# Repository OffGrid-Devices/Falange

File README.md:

# OffGrid-Devices Falange
Arduino-based delay weirdo

[BOM](https://docs.google.com/spreadsheets/d/1_OFgzQ-Cf3UgnrHv29c7YLzdb8jIv9dC1f2YYJAlo-E/edit?usp=sharing)

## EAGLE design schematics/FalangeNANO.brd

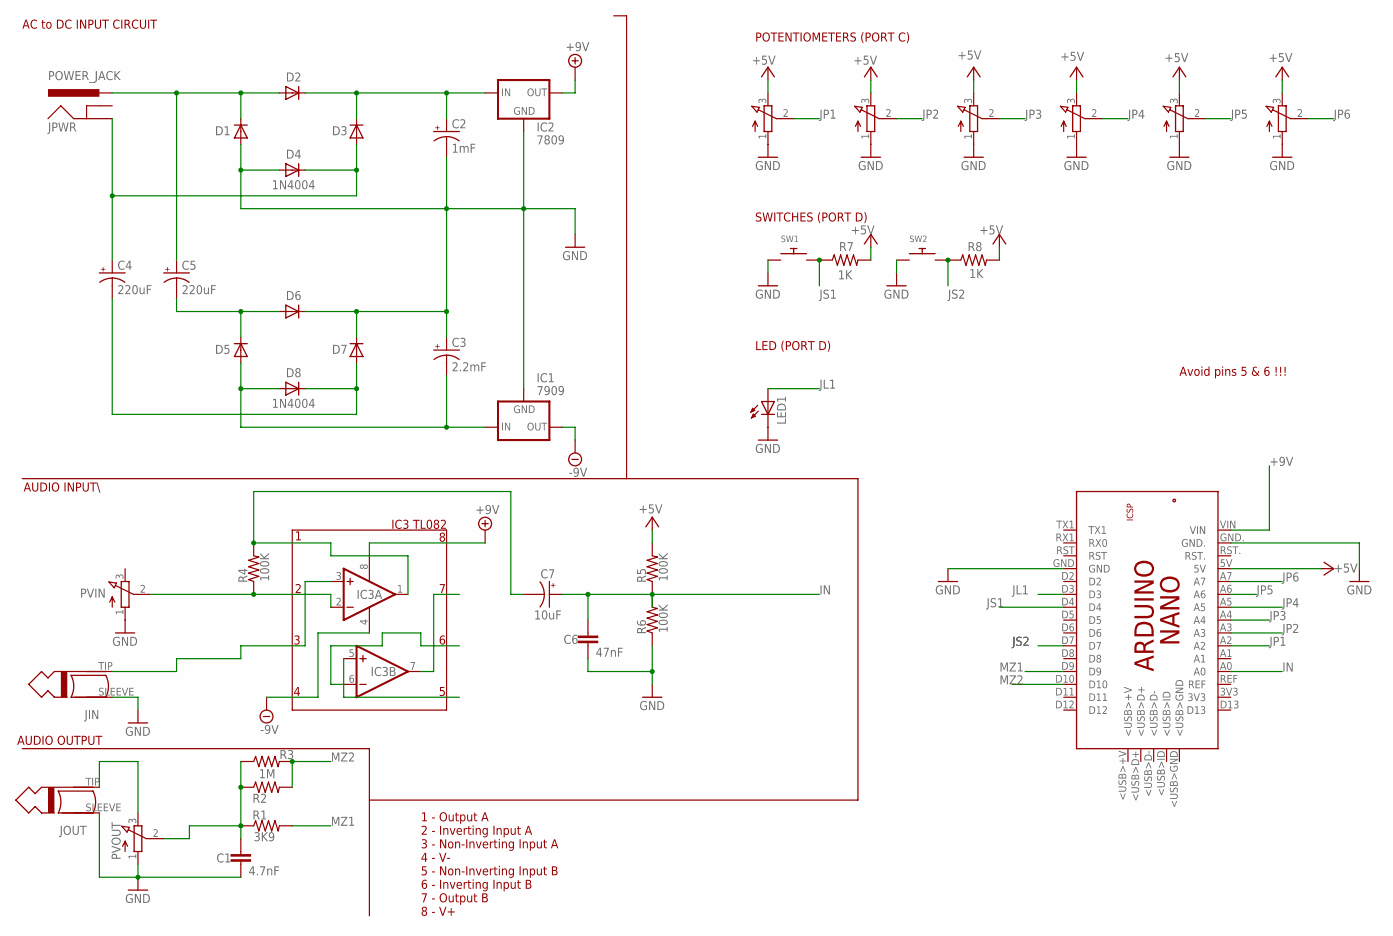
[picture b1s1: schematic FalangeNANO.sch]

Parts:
C1: 4.7nF; C050-025X075
C2: 1mF; E30-16
C3: 2.2mF; E35-16
C4, C5: 220uF; E5-10,5
C6: 47nF; C050-025X075
C7: 10uF; E2,5-6
D1, D2, D3, D4, D5, D6, D7, D8: 1N4004; DO41-10
IC1: 7909; 79XXL
IC2: 7809; 78XXL
IC3: TL082P; DIL08
JIN: MONO_PLUG; TWO_PADS
JOUT: MONO_PLUG; TWO_PADS
JPWR: POWER_JACK; POWER_JACK_PTH
LED1: LED3MM
P1, P2, P3, P4, P5, P6: 3RP/1610N
PCB1: ARDUINO_NANO
PVIN: 3RP/1610N
PVOUT: 3RP/1610N
R1: 3K9; AXIAL-0.3
R2, R3: 1M; AXIAL-0.3
R4, R5, R6: 100K; AXIAL-0.3
R7, R8: 1K; AXIAL-0.3
SW1, SW2: SWITCH_PUSHBUTTONEVQ-PE; TACT_PANA-EVQ

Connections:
+5V: P1.3 (E), P2.3 (E), P3.3 (E), P4.3 (E), P5.3 (E), P6.3 (E), PCB1.5V, R5.P$2 (2), R7.P$2 (2), R8.P$2 (2)
+9V: IC2.OUT, IC3.8 (V+), PCB1.VIN
-9V: IC1.OUT, IC3.4 (V-)
GND: C1.2, C2.-, C3.+, C6.2, D1.A, D4.A, D6.C, D7.C, IC1.GND, IC2.GND, JIN.SLEEVE, JOUT.SLEEVE, LED1.K (C), P1.1 (A), P2.1 (A), P3.1 (A), P4.1 (A), P5.1 (A), P6.1 (A), PCB1.GND, PCB1.GND., PVIN.1 (A), PVOUT.1 (A), R6.P$1 (1), SW1.P$1, SW2.P$1
IN: C6.1, C7.+, PCB1.A0, R5.P$1 (1), R6.P$2 (2)
JL1: LED1.A, PCB1.D3
JP1: P1.2 (S), PCB1.A2
JP2: P2.2 (S), PCB1.A3
JP3: P3.2 (S), PCB1.A4
JP4: P4.2 (S), PCB1.A5
JP5: P5.2 (S), PCB1.A6
JP6: P6.2 (S), PCB1.A7
JP8-2: C1.1, PVOUT.2 (S), R1.P$1 (1), R2.P$1 (1), R3.P$1 (1)
JP8-3: JOUT.TIP, PVOUT.3 (E)
JS1: PCB1.D4, R7.P$1 (1), SW1.P$2
JS2: PCB1.D7, R8.P$1 (1), SW2.P$2
MZ1: PCB1.D9, R1.P$2 (2)
MZ2: PCB1.D10, R2.P$2 (2), R3.P$2 (2)
unnamed: C5.-, D5.C, D6.A
unnamed: C4.-, D7.A, D8.C
unnamed: C2.+, D2.C, D3.C, IC2.IN
unnamed: C3.-, D5.A, D8.A, IC1.IN
unnamed: C7.-, IC3.1 (OUT), R4.P$2 (2)
unnamed: IC3.2 (-IN), PVIN.2 (S), R4.P$1 (1)
unnamed: IC3.3 (+IN), JIN.TIP
PWRSLV: C4.+, D3.A, D4.C, JPWR.GND
PWRTIP: C5.+, D1.C, D2.A, JPWR.PWR

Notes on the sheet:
AUDIO OUTPUT
AC to DC INPUT CIRCUIT
AUDIO INPUT\
IC3 TL082
1 - Output A 2 - Inverting Input A 3 - Non-Inverting Input A 4 - V- 5 - Non-Inverting Input B 6 - Inverting Input B 7 - Output B 8 - V+
POTENTIOMETERS (PORT C)
SWITCHES (PORT D)
LED (PORT D)
Avoid pins 5 & 6 !!!

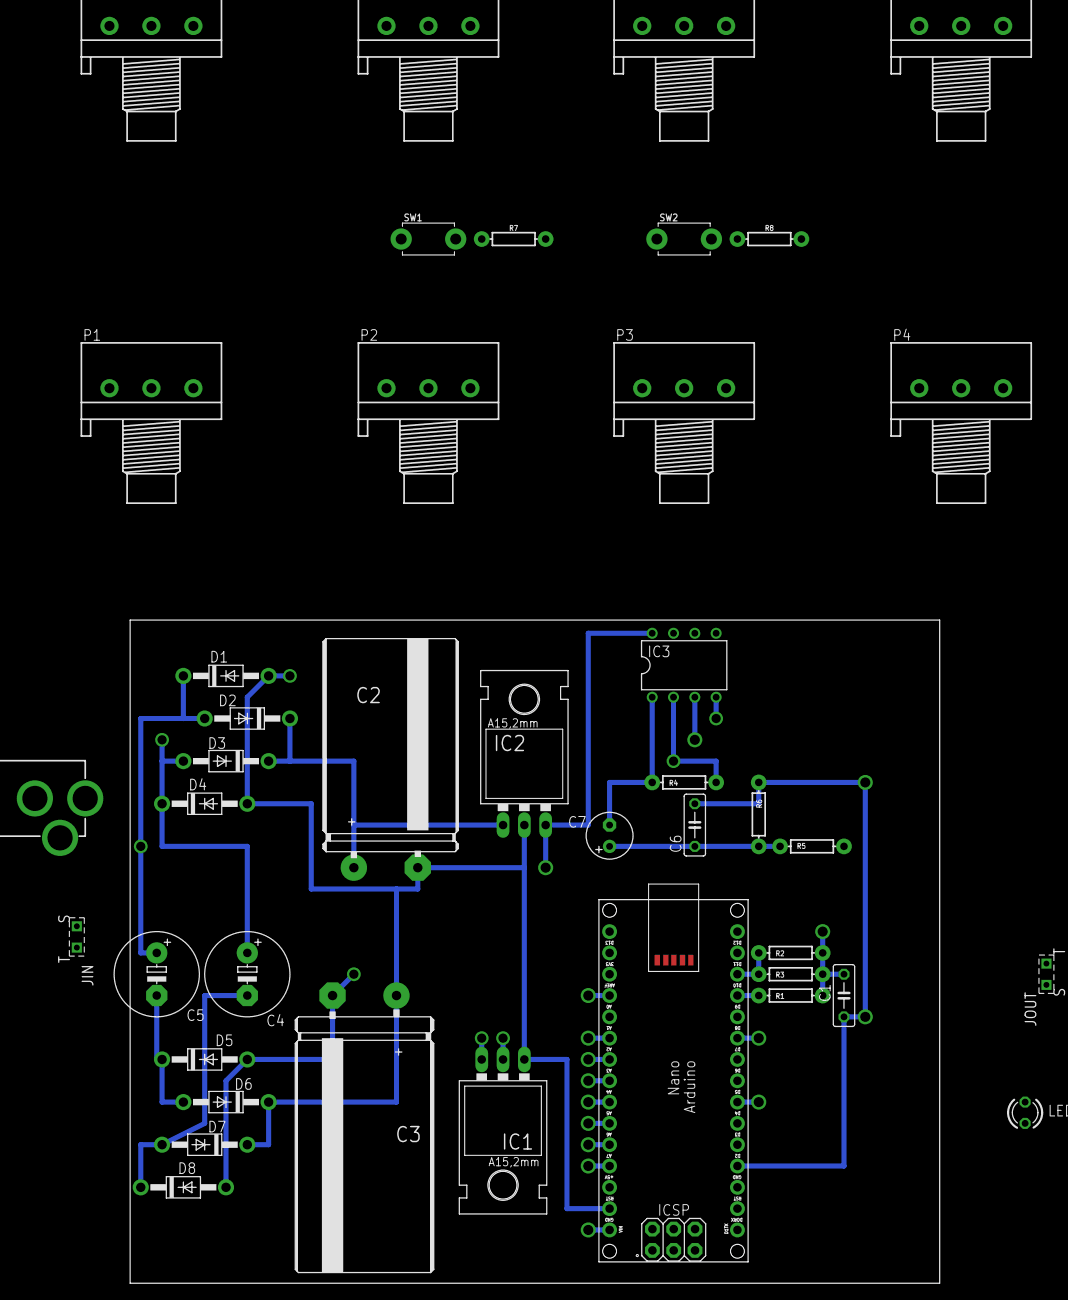
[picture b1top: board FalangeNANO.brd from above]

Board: 16 copper layers, 96.5 x 79.0 mm, 41 parts (0 on the bottom side), 27 nets.

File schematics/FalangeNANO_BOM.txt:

Partlist exported from C:/Users/tiago/Documents/GitHub/OffGrid-Devices/Falange/schematics/FalangeNANO.sch at 27-05-2018 14:49

Qty Value        Device                  Package        Parts                               Description                                                                                                                                                                                                           
8                3RP/1610N               3RP/1610N      P1, P2, P3, P4, P5, P6, PVIN, PVOUT 16mm Potentiometer one level                                                                                                                                                                                          
1                LED3MM                  LED3MM         LED1                                LED                                                                                                                                                                                                                   
2                SWITCH_PUSHBUTTONEVQ-PE TACT_PANA-EVQ  SW1, SW2                            Buttons                                                                                                                                                                                                               
3   100K         1KOHM-HORIZ-1/4W-5%     AXIAL-0.3      R4, R5, R6                          1kO resistor                                                                                                                                                                                                          
1   10uF         CPOL-USE2.5-6           E2,5-6         C7                                  POLARIZED CAPACITOR, American symbol                                                                                                                                                                                  
2   1K           1KOHM-HORIZ-1/4W-5%     AXIAL-0.3      R7, R8                              1kO resistor                                                                                                                                                                                                          
2   1M           1KOHM-HORIZ-1/4W-5%     AXIAL-0.3      R2, R3                              1kO resistor                                                                                                                                                                                                          
8   1N4004       1N4004                  DO41-10        D1, D2, D3, D4, D5, D6, D7, D8      DIODE                                                                                                                                                                                                                 
1   1mF          CPOL-USE30-16AXIAL      E30-16         C2                                  POLARIZED CAPACITOR, American symbol                                                                                                                                                                                  
1   2.2mF        CPOL-USE35-16AXIAL      E35-16         C3                                  POLARIZED CAPACITOR, American symbol                                                                                                                                                                                  
2   220uF        CPOL-USE5-10.5          E5-10,5        C4, C5                              POLARIZED CAPACITOR, American symbol                                                                                                                                                                                  
1   3K9          1KOHM-HORIZ-1/4W-5%     AXIAL-0.3      R1                                  1kO resistor                                                                                                                                                                                                          
1   4.7nF        C-EU050-025X075         C050-025X075   C1                                  CAPACITOR, European symbol                                                                                                                                                                                            
1   47nF         C-EU050-025X075         C050-025X075   C6                                  CAPACITOR, European symbol                                                                                                                                                                                            
1   7809         78XXL                   78XXL          IC2                                 VOLTAGE REGULATOR                                                                                                                                                                                                     
1   7909         79XXL                   79XXL          IC1                                 VOLTAGE REGULATOR                                                                                                                                                                                                     
1   ARDUINO_NANO ARDUINO_NANO            ARDUINO_NANO   PCB1                                Device for representing an Arduino Nano board with a footprint in an EAGLE design. Created by Dave Young for Element14. More EAGLE documentation at: http://www.element14.com/community/community/knode/cadsoft_eagle 
2   MONO_PLUG    MONO_PLUG               TWO_PADS       JIN, JOUT                                                                                                                                                                                                                                                 
1   POWER_JACK   POWER_JACK              POWER_JACK_PTH JPWR                                Power Jack Connector                                                                                                                                                                                                  
1   TL082P       TL082P                  DIL08          IC3                                 OP AMP

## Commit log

2018-05-23 uploaded Falange Lite
    The only difference from "Falange" is that it doesn't have support for a
    piezo direct connection bypassing the pre-amplifier
2018-05-23 uploaded Falange schematics
2018-05-27 added hardware test
2018-05-27 update falange schematics
2018-05-27 basic prototype
2018-05-27 this code wasn't working quite well
2019-09-03 version 0.1
2019-09-04 moving to version 0.2
    simple noise and selectable LP/HP filter
2019-09-04 simple filter implementation (LP/HP)
2019-09-04 implemented feedback delay
2019-09-04 kinda functional
    switch1 sets the filter pre or post delay
2019-09-04 implemented led blinking sync'd to LFO
2019-09-04 improved led function
2019-09-04 minor changes
2019-09-04 safe state
    starting to develop the final architecture
2019-09-05 tuned both LP & HP filters to their best sounding parameters
2019-09-05 implemented distortion modes
2019-09-05 some fixes
2019-09-05 some changes in distortion modes
2019-09-05 switch1 is now free
    the feedback delay certainly sounds better in the beginning of the chain
2019-09-05 compensation of random distortion volume
2019-09-05 updated hardware test to encompass circuit changes
    circuit changes: pin A7 has went bananas...moved to pin A1
2019-09-05 add 6 LFO waveforms
2019-09-05 modulations#1
    - implemented LFO>DelaySize modulatino on switch1
    - implemented constrained feedback levels on modulation knob
2019-09-05 implemented resonance control
2019-09-05 now added audio input
2019-09-06 final

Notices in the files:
parts and their libraries:
SparkFun-Connectors: Licensing: Creative Commons ShareAlike 4.0 International - https://creativecommons.org/licenses/by-sa/4.0
